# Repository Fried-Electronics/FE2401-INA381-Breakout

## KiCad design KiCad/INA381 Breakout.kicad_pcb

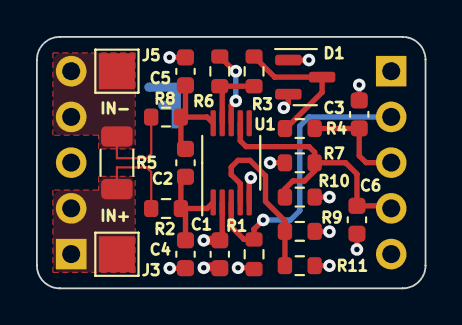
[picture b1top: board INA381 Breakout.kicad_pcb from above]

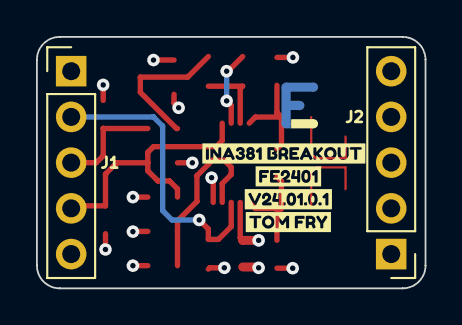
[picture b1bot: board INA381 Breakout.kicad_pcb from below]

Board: 4 copper layers, 21.6 x 14.0 mm, 27 parts (6 on the bottom side), 13 nets.

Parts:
C1, C2, C4, C5: 100nF; C_0603_1608Metric
C3: 10nF; C_0603_1608Metric
C6: 1uF; C_0603_1608Metric
D1: BAT54S; SOT-23
J1, J2: Conn_01x05; PinHeader_1x05_P2.54mm_Vertical
J3: IN+; TestPoint_Pad_2.0x2.0mm
J5: IN-; TestPoint_Pad_2.0x2.0mm
R1, R7, R10: 10k; R_0603_1608Metric
R2, R8: 10R; R_0603_1608Metric
R3: 100R; R_0603_1608Metric
R4, R6, R9, R11: 0R; R_0603_1608Metric
R5: 0.020R; R_1206_3216Metric
U1: INA381; VSSOP-10_3x3mm_P0.5mm
kibuzzard-659961C4: G***; kibuzzard-659961C4
kibuzzard-6599620A: G***; kibuzzard-6599620A
kibuzzard-65996276: G***; kibuzzard-65996276
kibuzzard-65996284: G***; kibuzzard-65996284

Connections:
/CMPIN: R6.2, U1.8 (CMPIN)
/CMPREF: C6.1, J1.4, R7.2, R10.1, U1.7 (CMPREF)
/IN+: C2.1, C4.1, R2.2, U1.1 (IN+)
/IN-: C2.2, C5.1, R8.2, U1.10 (IN-)
/RES+: J2.1, J2.2, J3.1, R2.1, R5.1
/RES-: J2.4, J2.5, J5.1, R5.2, R8.1
/RESET: R9.2, R11.1, U1.4 (RESET)
/VOUT: R3.1, R6.1, U1.9 (VOUT)
/~ALERT: J1.2, R1.2, U1.3 (~ALERT)
GND: C1.1, C3.2, C4.2, C5.2, C6.2, D1.1 (A), J1.5, R10.2, R11.2, U1.5 (GND)
unnamed: D1.3 (COM), R3.2, R4.1
unnamed: C3.1, J1.3, R4.2
VDD: C1.2, D1.2 (K), J1.1, R1.1, R7.1, R9.1, U1.2 (VS+)

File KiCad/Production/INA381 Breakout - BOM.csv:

"Source:","C:\Users\tomfr\Documents\GitHub\FE2401-INA381-Breakout\KiCad\INA381 Breakout.kicad_sch"
"Date:","07/01/2024 19:55:46"
"Tool:","Eeschema 7.0.9"
"Generator:","C:\Program Files\KiCad\7.0\bin\scripting\plugins/bom_csv_grouped_by_value.py"
"Component Count:","21"

"Collated Components:"

"Item","Qty","Reference(s)","Value","LibPart","Footprint","Datasheet","DNP","Manufacturer Part Number","Mouser Part Number"
"1","4","C1, C2, C4, C5","100nF","Device:C_Small","Capacitor_SMD:C_0603_1608Metric","~","","885012206095","710-885012206095"
"2","1","C3","10nF","Device:C_Small","Capacitor_SMD:C_0603_1608Metric","~","","CL10B103KB8NNNL","187-CL10B103KB8NNNL"
"3","1","C6","1uF","Device:C_Small","Capacitor_SMD:C_0603_1608Metric","~","","CL10B105KB8NQNC","187-CL10B105KB8NQNC"
"4","1","D1","BAT54S","friedElectronicsSymbols:BAT54S","Package_TO_SOT_SMD:SOT-23","https://www.diodes.com/assets/Datasheets/ds11005.pdf","","BAT54S-7-F","621-BAT54S-F"
"5","2","J1, J2","Conn_01x05","Connector_Generic:Conn_01x05","Connector_PinHeader_2.54mm:PinHeader_1x05_P2.54mm_Vertical","~","","10129378-905001BLF","649-1012937890501BLF"
"6","3","R1, R7, R10","10k","Device:R_Small","Resistor_SMD:R_0603_1608Metric","~","","RN73R1JTTD1002B25","660-RN73R1JTD1002B25"
"7","2","R2, R8","10R","Device:R_Small","Resistor_SMD:R_0603_1608Metric","~","","CRT0603-BY-10R0ELF","652-CRT0603BY10R0ELF"
"8","1","R3","100R","Device:R_Small","Resistor_SMD:R_0603_1608Metric","~","","RN73R1JTTD1000B25","660-RN73R1JTD1000B25"
"9","3","R4, R6, R11","0R","Device:R_Small","Resistor_SMD:R_0603_1608Metric","~","","RC0603JR-070RL","603-RC0603JR-070RL"
"10","1","R5","0.020R","Device:R_Small","Resistor_SMD:R_1206_3216Metric","~","","MFL1206R0200FS","504-MFL1206R0200FS"
"11","1","R9","0R","Device:R_Small","Resistor_SMD:R_0603_1608Metric","~","DNP","RC0603JR-070RL","603-RC0603JR-070RL"
"12","1","U1","INA381","friedElectronicsSymbols:INA381","Package_SO:VSSOP-10_3x3mm_P0.5mm","","","INA381A2IDGSR","595-INA381A2IDGSR"

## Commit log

2024-01-07 Created KiCad project
2024-01-08 added BOM
2024-01-18 Added ADC oversample STM32 code
    oversample the ADC pin on PA0 using the hardware oversampler by 256
    connect PA0 to PA4 to connect the DAC to the ADC
    ADC output is streamed over serial port
2024-01-26 moved IBOM
